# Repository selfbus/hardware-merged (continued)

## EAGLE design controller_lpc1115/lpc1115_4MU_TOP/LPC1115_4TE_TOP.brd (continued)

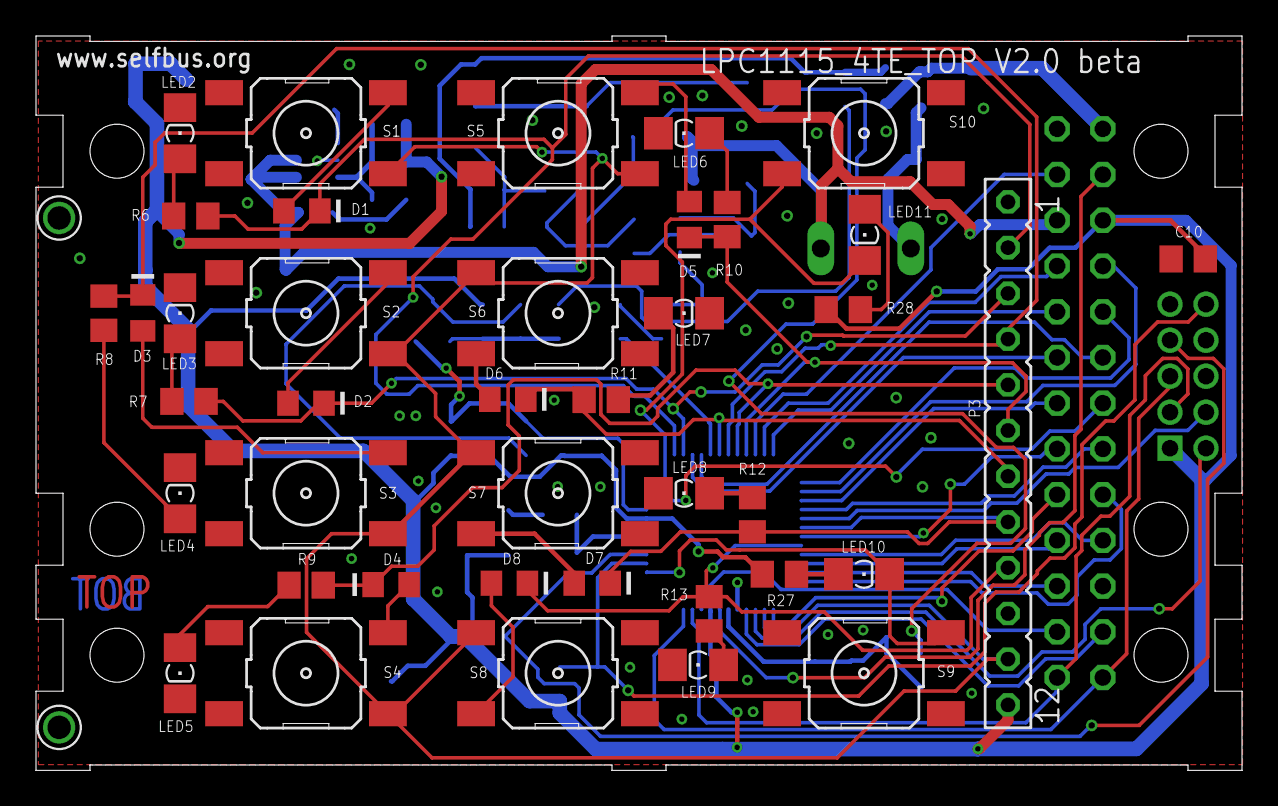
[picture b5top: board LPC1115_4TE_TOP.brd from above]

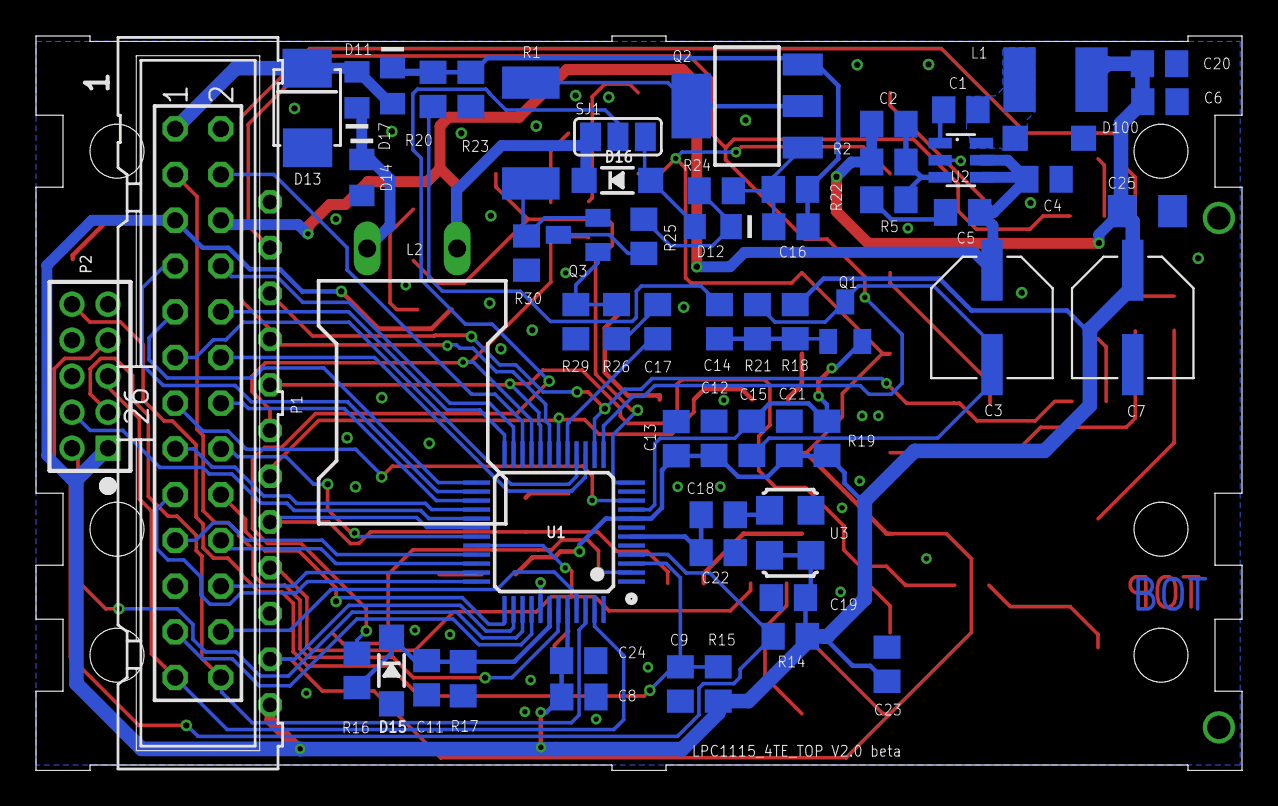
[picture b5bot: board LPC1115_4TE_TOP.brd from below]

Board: 2 copper layers, 67.0 x 40.8 mm, 103 parts (61 on the bottom side), 79 nets.

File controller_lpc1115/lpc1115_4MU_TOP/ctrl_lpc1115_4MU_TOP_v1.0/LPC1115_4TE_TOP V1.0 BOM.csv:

"Qty","Value","Package","Parts","Anmerkung","Lieferant","Bestellartikel","Artikelpreis","VPE","Postenpreis"
1,,"Platine LPC115_4TE_TOP",,,,,,,
1,,"ML26","P1",,"Reichelt","SL 2X13G 2,54","0,12",1,"0,12"
1,,"Pfostenbuchse 2x13pol 2,54mm",,,"Reichelt","PFL 26","0,19",1,"0,19"
1,"ISP","PINHD-2X05_2.00mm","P2",,"Reichelt","MPE 150-3-010","0,2",1,"0,2"
0,,"FE-1X12_2.54mm","P3","nur benötigt, wenn Bedienplatine aufgesteckt werden soll!","Reichelt","MPE 094-1-016","0,31",1,0
2,"18p","C-EUC0805M","C20, C21","wenn Quarz verwendet wird, vermutlich passen auch 15pF","TME","CC0805JRNPO9BN180","0,00973",1,"0,01946"
2,"100p","C-EUC0805M","C15, C18","C18: wenn Oszillator verwendet wird","Reichelt","NPO-G0805 100P","0,04",1,"0,08"
1,"220p","C-EUC0805M","C22","wenn Oszillator verwendet wird","Reichelt","NPO-G0805 220P","0,04",1,"0,04"
3,"10n","C-EUC0805M","C9, C16, C17"," ","Reichelt","X7R-G0805 10N","0,04",1,"0,12"
1,"10n(*)","C-EUC0805M","C11","Applikationsabhängig","Reichelt","X7R-G0805 10N","0,04",1,"0,04"
1,"15nF","C-EUC0805M","C1",,"Reichelt","X7R-G0805 15N","0,04",1,"0,04"
7,"100n","C-EUC0805M","C5, C8, C10, C12, C14, C19, C23",,"Reichelt","X7R-G0805 100N","0,04",1,"0,28"
1,"220n","C-EUC0805M","C2",,"Reichelt","X7R-G0805 0,22µ","0,04",1,"0,04"
1,"1µ/16V","C-EUC0805M","C13",,"Reichelt","X7R-G0805 1,0/16","0,04",1,"0,04"
1,"4.7µF/50V","C-EUC1206M","C4",,"Reichelt","X7R-G1206 4,7/50","0,23",1,"0,23"
1,"22µ/10V","C-EUC1210K","C6"," ","Reichelt","X7R-G1206 22/10","0,19",1,"0,19"
1,"FV 100/35 K-D8","CPOL-EUUD-6,3X7,7","C3",,"Reichelt","VF 100/35 K-D8","0,18",1,"0,18"
0,"100µ(*)","CPOL-EUUD-6,3X7,7","C7","abhängig vom Strombedarf der Applikation","Reichelt","VF 100/35 K-D8","0,18",1,0
1,"6.8µH","IND_FASTRON_1616FPSB","L1",,"Reichelt","L-1616FPS 6,8µ","0,3",1,"0,3"
1,"150mH","SD12BS11_LIEGEND","L2",,"Reichelt","L-11P 150M","0,55",1,"0,55"
1,"5R6","R-EU_R1206M","R30","RESISTOR, European symbol","Reichelt","SMD 1/4W 5,6","0,05",1,"0,05"
1,"680R","R-EU_R0805M","R5","RESISTOR, European symbol","Reichelt","SMD-0805 680","0,03",1,"0,03"
2,"1k","R-EU_R0805M","R22, R24","RESISTOR, European symbol","Reichelt","SMD-0805 1,00K","0,03",1,"0,06"
11,"1k5","R-EU_R0805M","R3, R6, R7, R8, R9, R10, R11, R12, R13, R27, R28","RESISTOR, European symbol","Reichelt","SMD-0805 1,50K","0,03",1,"0,33"
1,"2k2","R-EU_R0805M","R25","RESISTOR, European symbol","Reichelt","SMD-0805 2,20K","0,03",1,"0,03"
1,"2k4","R-EU_R0805M","R2","RESISTOR, European symbol","Reichelt","RND 0805 1 2,4K","0,02",1,"0,02"
1,"5k6","R-EU_R0805M","R26","RESISTOR, European symbol","Reichelt","SMD-0805 5,60K","0,03",1,"0,03"
2,"10k","R-EU_R0805M","R19, R20","RESISTOR, European symbol","Reichelt","SMD-0805 10,0K","0,03",1,"0,06"
1,"3k(*)","R-EU_R0805M","R17","RESISTOR, European symbol","Reichelt","RND 0805 1 3k0","0,02",1,"0,02"
1,"15k","R-EU_R0805M","R4","RESISTOR, European symbol","Reichelt","SMD-0805 15,0K","0,03",1,"0,03"
1,"47k","R-EU_R0805M","R21","RESISTOR, European symbol","Reichelt","SMD-0805 47,0K","0,03",1,"0,03"
1,"82k","R-EU_R0805M","R18","RESISTOR, European symbol","Reichelt","SMD-0805 82,0K","0,03",1,"0,03"
1,"36k(*)","R-EU_R0805M","R16","RESISTOR, European symbol","Reichelt","RND 0805 1 36k","0,02",1,"0,02"
4,"100k","R-EU_R0805M","R14, R15, R23, R29","RESISTOR, European symbol","Reichelt","SMD-0805 100K","0,03",1,"0,12"
1,"390k","R-EU_R0805M","R1","RESISTOR, European symbol","Reichelt","SMD-0805 390K","0,03",1,"0,03"
0,"SMAJ40CA","D-SMB","D13","nur wenn auf der Applikationsplatine keine vorhanden ist","Oldis Shop","SMAJ 40 AC Überspannungsdiode","0,2",1,0
12,"TS4148","DIODE-MINIMELF","D1, D2, D3, D4, D5, D6, D7, D8, D11, D12, D14, D17"," ","Reichelt","TS 4148-1206","0,04",1,"0,48"
0,"RB060M-60(*)","DIODE-SOD123","D9","nicht bestückt, es wird D10 verwendet",,,0,0,0
1,"STPS1L60A","DIODE-SMB","D10"," ","TME","STPS1L60A","0,089",1,"0,089"
0,"(*)","DIODE-MINIMELF","D15","Zenerdiode applikationsabhängig","Reichelt","SMD ZF 3,6","0,04",1,0
1,"7V5","ZENER-DIODESOT23","D16",,"Reichelt","SMD ZD 7,5","0,04",1,"0,04"
8,"grün","LEDSMT1206","LED2, LED3, LED4, LED5, LED6, LED7, LED8, LED9","extra helle LEDs, benötigen daher nur wenig Strom","Reichelt","LED EL 1206 GR2","0,12",1,"0,96"
2,"red","LEDSMT1206","LED1, LED10, LED11","üblicherweise wird nur eine der LEDs LED10, LED11 bestückt","Reichelt","LED EL 1206 RT","0,1",1,"0,2"
1,"BC856","BC856BSMD","Q1",,"Reichelt","BC 856B SMD","0,04",1,"0,04"
1,"BCP52","SOT223","Q2",,"Reichelt","BCP 52-16 SMD","0,14",1,"0,14"
1,"BC847C","BC847","Q3 (in V1.0 bedruckt mit T1)",,"Reichelt","BC 847C SMD","0,04",1,"0,04"
0,,"10-XXSMD","S1, S2, S3, S4, S5, S6, S7, S8","Benötigte Länge des Tasters abhängig von Applikation! (7mm ist Minimum, eher 8)","Reichelt","TASTER 9316","0,23",1,0
8,,"10-XXSMD","S1, S2, S3, S4, S5, S6, S7, S8","Taster 9318 8mm (Länge für out6-cs, jedoch nur 6 Stück notwendig)","Reichelt","TASTER 9318","0,21",1,"1,68"
1,"Prog","10-XXSMD","S9, S10","üblicherweise wird nur einer der beiden Taster bestückt","Reichelt","TASTER 9315","0,15",1,"0,15"
1,"LPC1115FBD48","LPC1113/4/5_QFP48_XLSERIES","U1","LPC1115FBD48 (auch bei TME zu bekommen)","Oldis Shop","NXP LPC1115","2,5",1,"2,5"
1,"BD9G101","BD9G101G-SOT23-6","U2","Schaltregler","Oldis Shop","Schaltregler BD9G101G-CT-ND","1,5",1,"1,5"
1,"XO32 12MHz","ASFL","U3","CRYSTAL CLOCK OSCILLATORS","Reichelt","XO32 12,00000","1,3",1,"1,3"
0,"12MHz","CRYSTALASF","X1","Quarz alternativ zum Oszillator! Der Reichelt-Typ hat 12pF statt 10pF Nenn","Reichelt","12,000000-MT","0,95",1,0
10,,,,"Lichtleiter 4,7mm (für out6-cs nur 8 Stück notwendig)","Conrad",183133,"0,65",1,"6,5"

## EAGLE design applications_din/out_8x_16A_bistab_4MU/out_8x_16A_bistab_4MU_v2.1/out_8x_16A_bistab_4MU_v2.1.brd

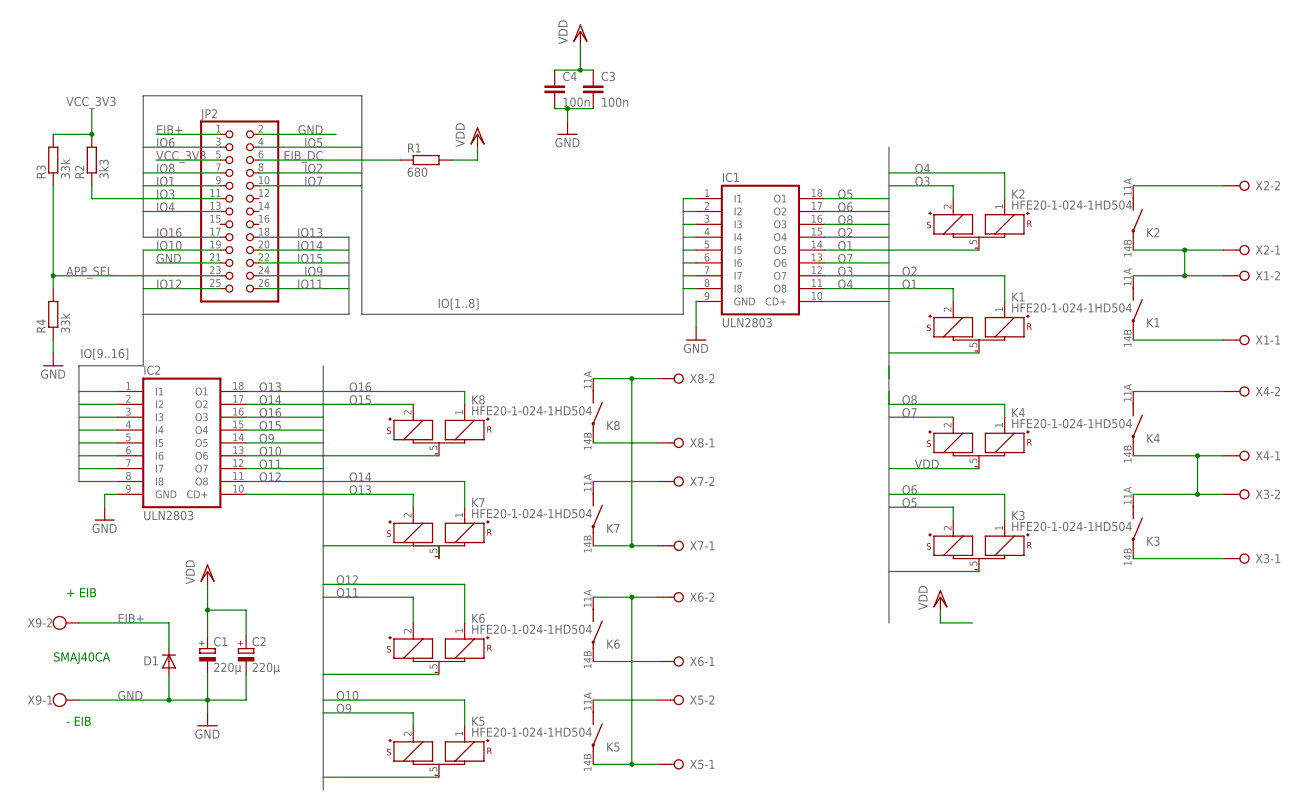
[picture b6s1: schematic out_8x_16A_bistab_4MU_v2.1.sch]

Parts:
C1, C2: 220µ; E3,5-8
C3, C4: 100n; C1206
D1: D-SMB; SMB
IC1, IC2: ULN2803; SO18W
JP2: PINHD-2X13_2.54-SMD; 2X13SMD
K1, K2, K3, K4, K5, K6, K7, K8: HFE20-1-024-1HD504; HFE20-3-504
R1: 680; M1206
R2: 3k3; M1206
R3, R4: 33k; M1206
X1, X2, X3, X4, X5, X6, X7, X8: W237-02P; W237-132
X9: W237-102

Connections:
APP_SEL: JP2.23, R3.1, R4.2
EIB+: D1.1 (C), JP2.1, X9.2
EIB_DC: JP2.6, R1.1
GND: C1.-, C2.-, C3.2, C4.2, D1.2 (A), IC1.9 (GND), IC2.9 (GND), JP2.2, JP2.21, R4.1, X9.1
IO1: IC1.5 (I5), JP2.9
IO2: IC1.4 (I4), JP2.8
IO3: IC1.7 (I7), JP2.11, R2.1
IO4: IC1.8 (I8), JP2.13
IO5: IC1.1 (I1), JP2.4
IO6: IC1.2 (I2), JP2.3
IO7: IC1.6 (I6), JP2.10
IO8: IC1.3 (I3), JP2.7
IO9: IC2.5 (I5), JP2.24
IO10: IC2.6 (I6), JP2.19
IO11: IC2.7 (I7), JP2.26
IO12: IC2.8 (I8), JP2.25
IO13: IC2.1 (I1), JP2.18
IO14: IC2.2 (I2), JP2.20
IO15: IC2.4 (I4), JP2.22
IO16: IC2.3 (I3), JP2.17
K12: K1.11A (PB), K2.14B (PA), X1.2, X2.1
K34: K3.11A (PB), K4.14B (PA), X3.2, X4.1
K56: K5.14B (PA), K6.11A (PB), X5.1, X6.2
K78: K7.14B (PA), K8.11A (PB), X7.1, X8.2
unnamed: K4.11A (PB), X4.2
unnamed: K8.14B (PA), X8.1
unnamed: K1.14B (PA), X1.1
unnamed: K3.14B (PA), X3.1
unnamed: K2.11A (PB), X2.2
unnamed: K7.11A (PB), X7.2
unnamed: K5.11A (PB), X5.2
unnamed: K6.14B (PA), X6.1
O1: IC1.14 (O5), K1.2 (S+)
O2: IC1.15 (O4), K1.1 (R+)
O3: IC1.12 (O7), K2.2 (S+)
O4: IC1.11 (O8), K2.1 (R+)
O5: IC1.18 (O1), K3.2 (S+)
O6: IC1.17 (O2), K3.1 (R+)
O7: IC1.13 (O6), K4.2 (S+)
O8: IC1.16 (O3), K4.1 (R+)
O9: IC2.14 (O5), K5.2 (S+)
O10: IC2.13 (O6), K5.1 (R+)
O11: IC2.12 (O7), K6.2 (S+)
O12: IC2.11 (O8), K6.1 (R+)
O13: IC2.18 (O1), K7.2 (S+)
O14: IC2.17 (O2), K7.1 (R+)
O15: IC2.15 (O4), K8.2 (S+)
O16: IC2.16 (O3), K8.1 (R+)
VCC_3V3: JP2.5, R2.2, R3.2
VDD: C1.+, C2.+, C3.1, C4.1, IC1.10 (CD+), IC2.10 (CD+), K1.5 (-), K2.5 (-), K3.5 (-), K4.5 (-), K5.5 (-), K6.5 (-), K7.5 (-), K8.5 (-), R1.2

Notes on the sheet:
+ EIB
- EIB
SMAJ40CA

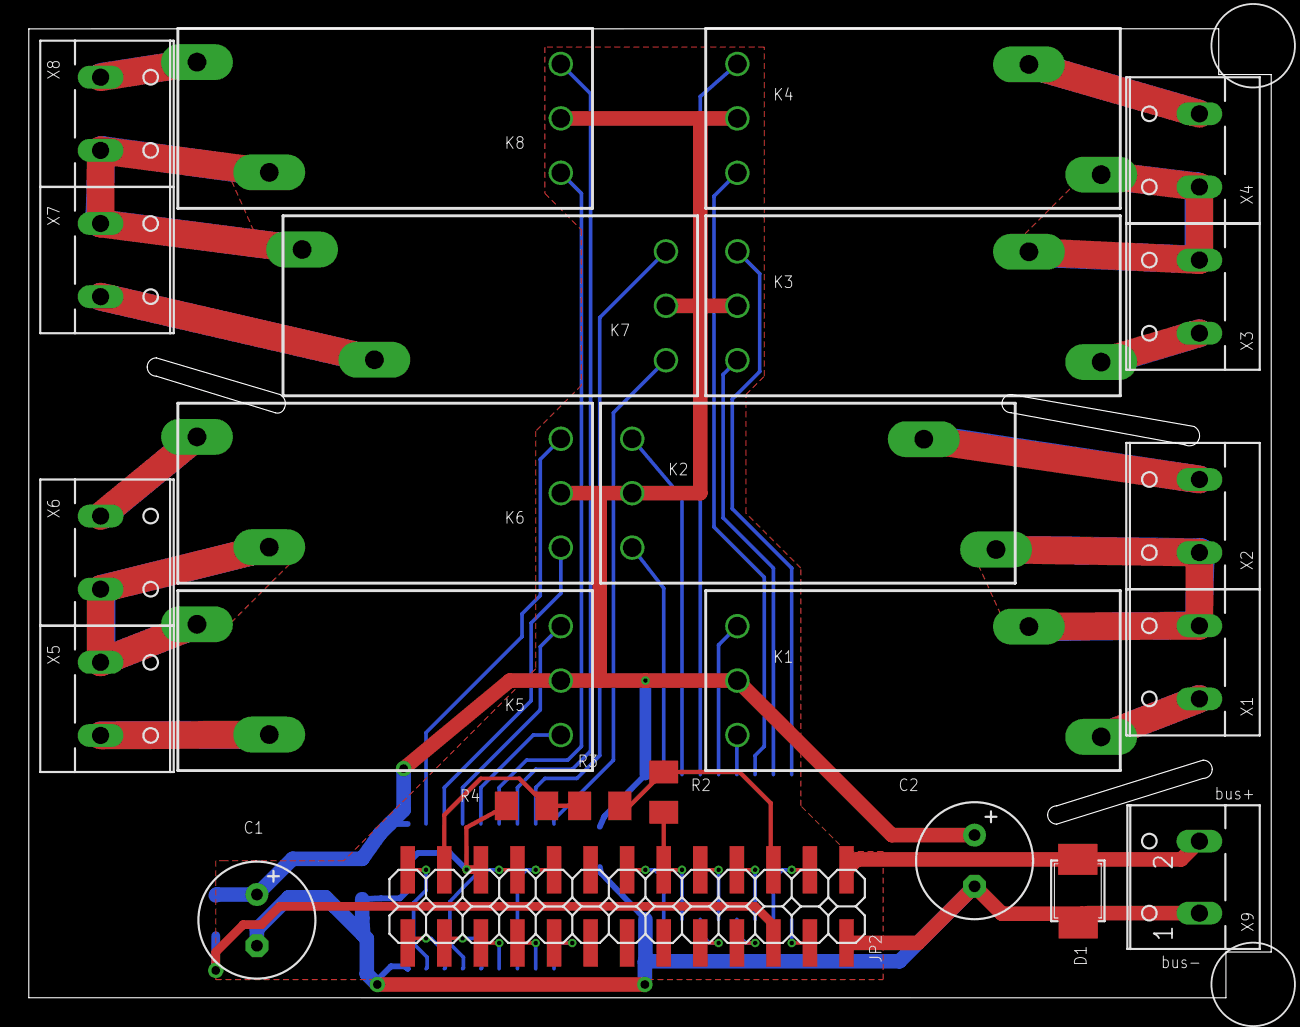
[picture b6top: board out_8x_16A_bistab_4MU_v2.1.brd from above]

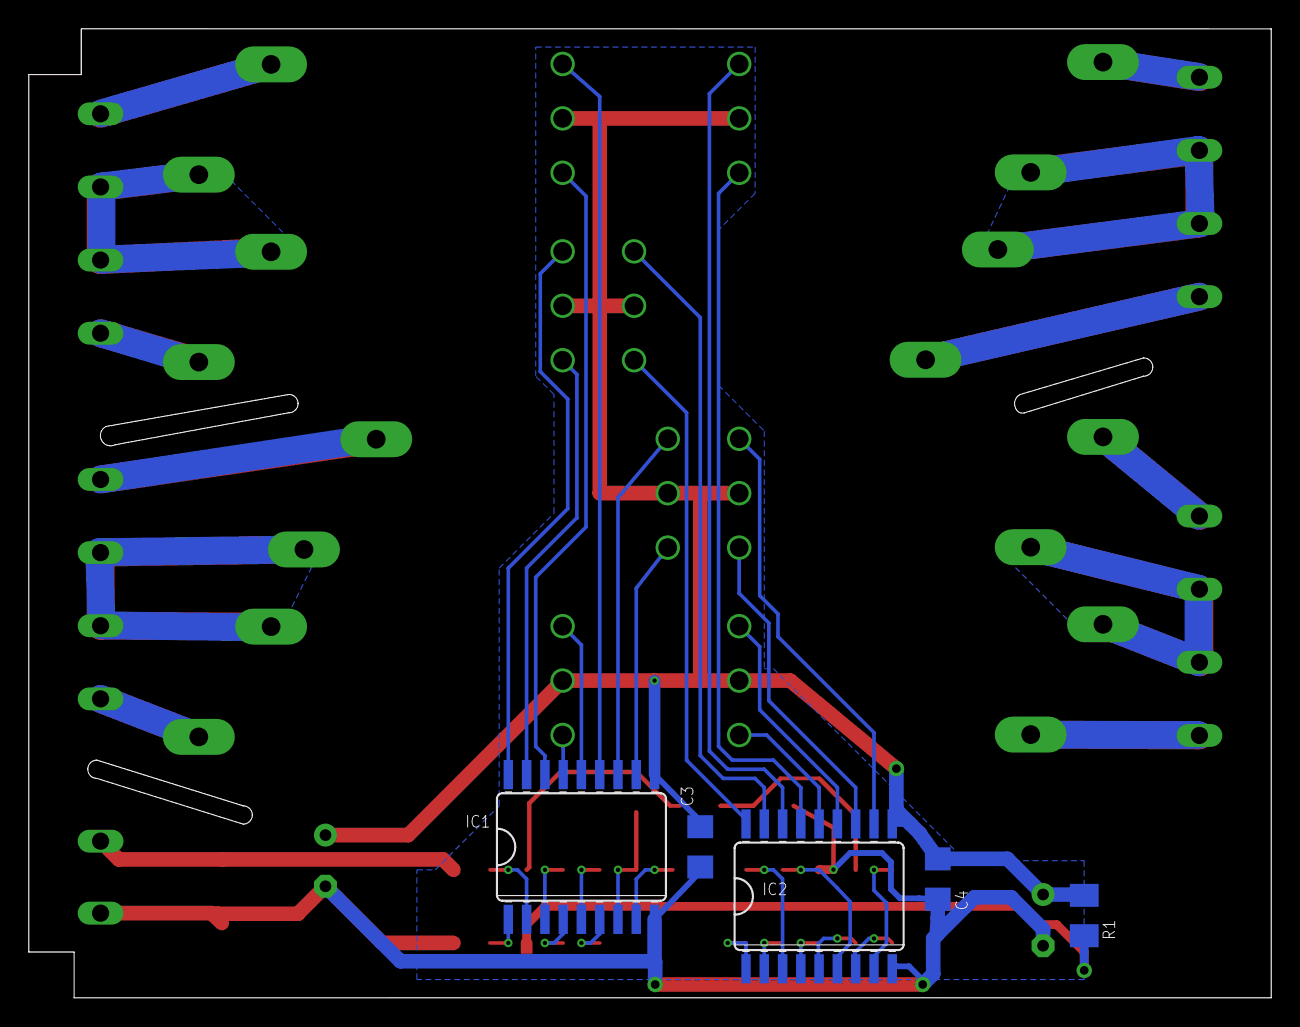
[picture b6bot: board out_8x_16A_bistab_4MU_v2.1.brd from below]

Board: 2 copper layers, 86.3 x 67.3 mm, 30 parts (5 on the bottom side), 50 nets.

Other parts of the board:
U$1: HUT4C-NO-DRILL

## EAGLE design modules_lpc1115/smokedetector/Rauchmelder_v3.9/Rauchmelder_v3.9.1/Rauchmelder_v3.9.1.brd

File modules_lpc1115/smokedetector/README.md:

<h1>KNX interface for Gira Dual Q smoke detectors</h1>

This module is a well tested interface to get your Dual Q smoke detectors connected to your KNX bus. 

The unversioned Rauchmelder.sch and Rauchmelder.brd files are the development files. 
Once a new version is released, a corresponding copy of the files with the release version appended to the file name are provided. 

Project documentation: https://selfbus.org/wiki/devices/sensors/6-smoke-detector-module </br>
Forum discussions: https://selfbus.org/forum/app.php/tag/Rauchmelder

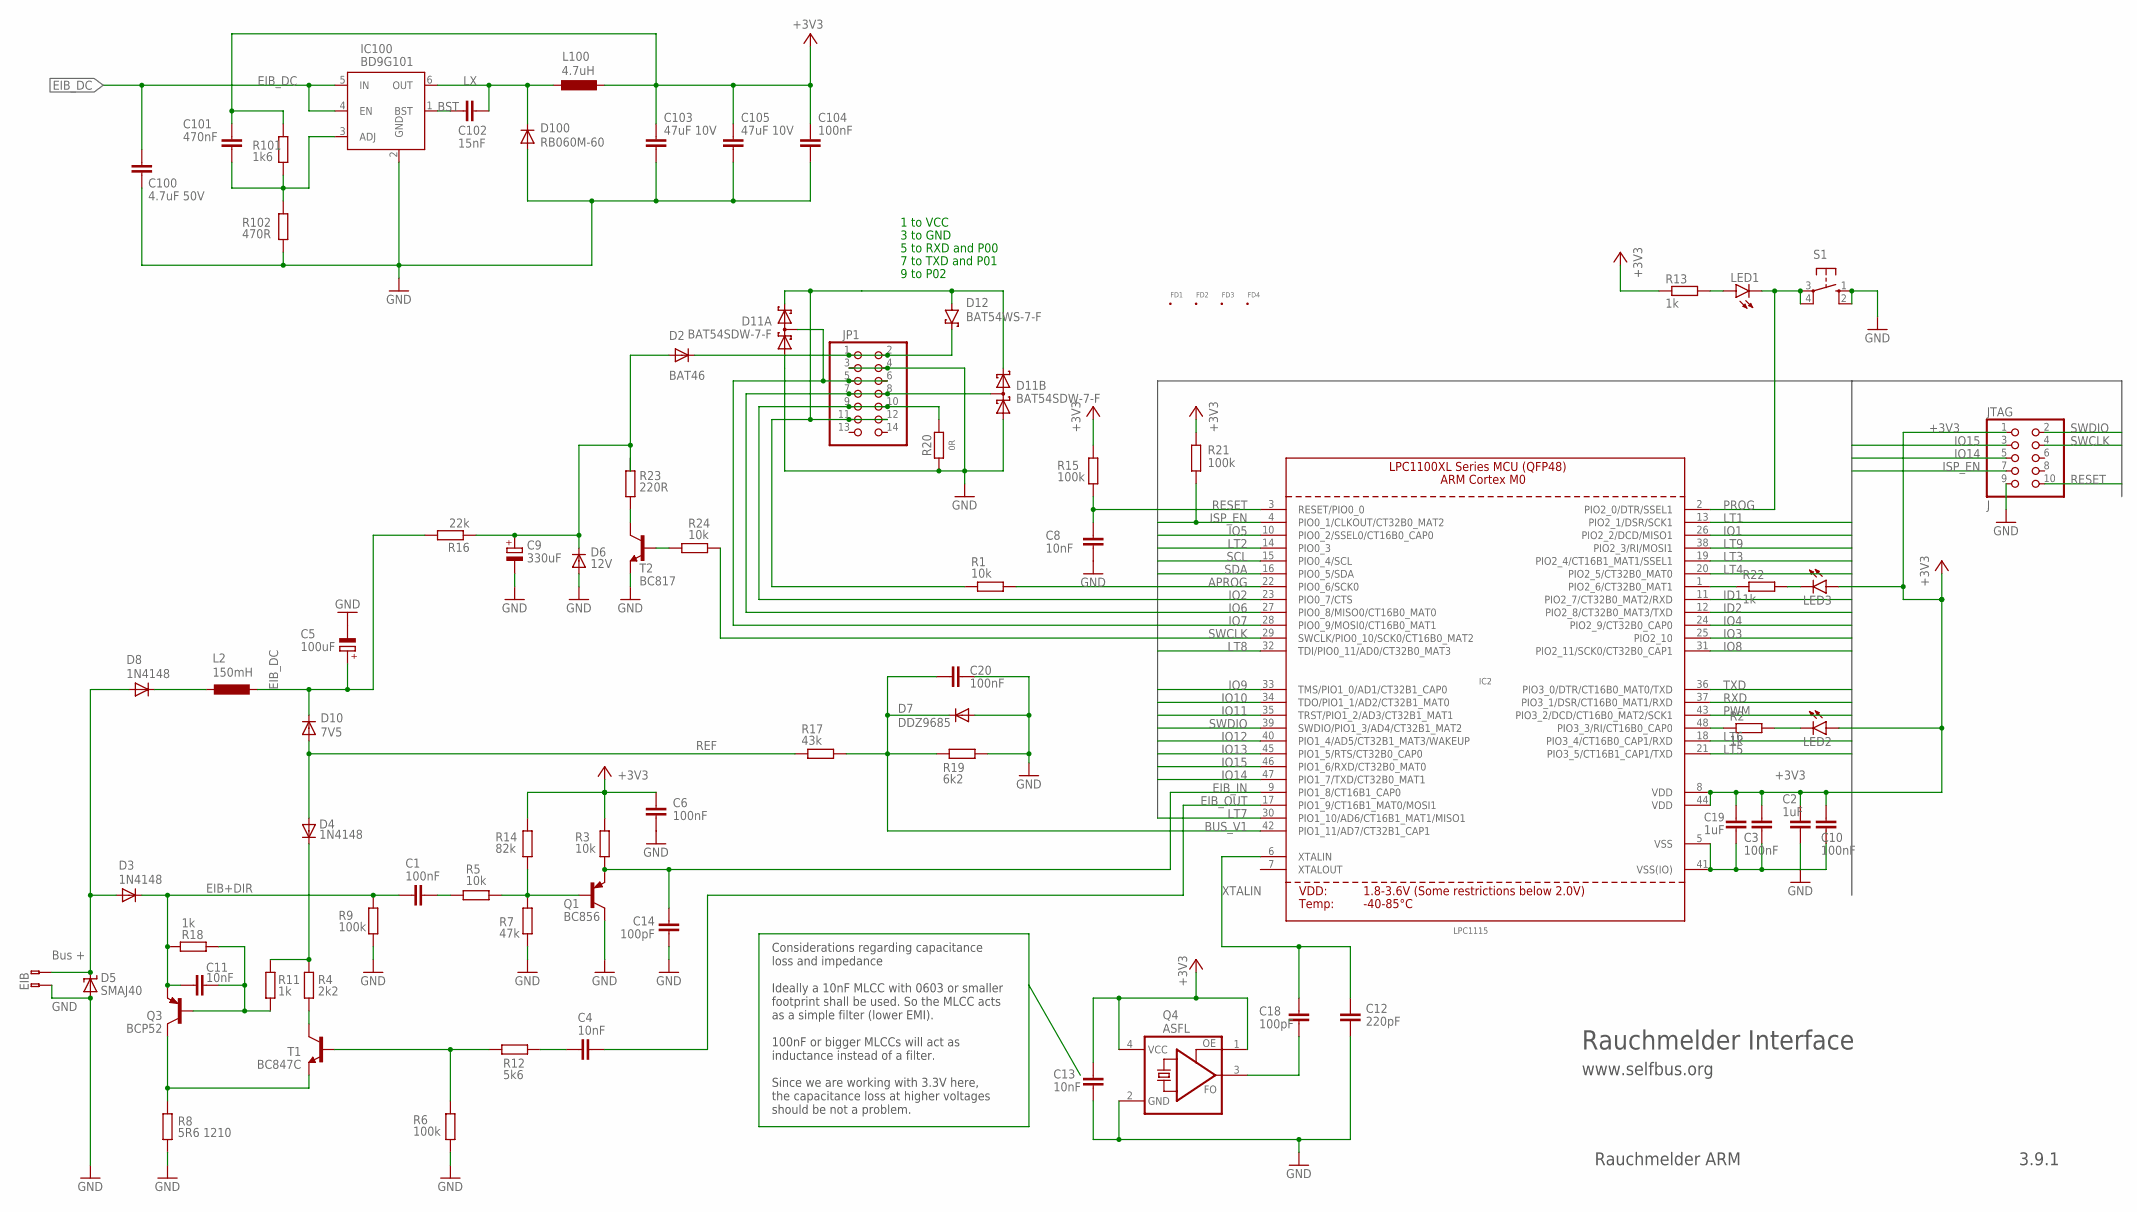
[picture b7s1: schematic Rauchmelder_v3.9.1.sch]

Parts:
C1, C3, C6, C10, C20, C104: 100nF; C0805
C2, C19: 1uF; C0805
C4, C8, C11, C13: 10nF; C0805
C5: 100uF; SANYO-OSCON_SMD_C6
C9: 330uF; E3,5-8
C12: 220pF; C0805
C14, C18: 100pF; C0805
C100: 4.7uF 50V; C1210
C101: 470nF; C0805
C102: 15nF; C0805
C103, C105: 47uF 10V; C0805
D2: BAT46; SOD-123
D3, D4, D8: 1N4148; SOD-123
D5: SMAJ40; SMBJ
D6: 12V; SOD-123
D7: DDZ9685; SOD-123
D10: 7V5; SOD-123
D11: BAT54SDW-7-F; SOT363
D12: BAT54WS-7-F; SOD323
D100: RB060M-60; SOD-123
FD1, FD2, FD3, FD4: FID_40MIL; FID_040
IC2: LPC1115; LQFP48
IC100: BD9G101; SOT23-6
JP1: PINHD-2X7; 2X07
JTAG: J; 2X05M
L2: 150mH; 11P-L1
L100: 4.7uH; L4532P
LED1, LED2, LED3: LEDCHIPLED_0805; CHIPLED_0805
Q1: BC856; SOT23-BEC
Q3: BCP52; SOT223
Q4: ASFL; ASF
R1, R3, R5, R24: 10k; R0805
R2, R11, R13, R18, R22: 1k; R0805
R4: 2k2; R0805
R6, R9, R15, R21: 100k; R0805
R7: 47k; R0805
R8: 5R6 1210; R1210
R12: 5k6; R0805
R14: 82k; R0805
R16: 22k; R0805
R17: 43k; R0805
R19: 6k2; R0805
R20: 0R; R0805
R23: 220R; R2512
R101: 1k6; R0805
R102: 470R; R0805
S1: 10-XX; B3F-10XX
T1: BC847C; SOT23
T2: BC817; SOT23-WIDE
U$1: EIB; BUSKLEMME243-724

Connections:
+3V3: C2.2, C3.2, C6.2, C10.2, C13.2, C19.2, C101.2, C103.1, C104.1, C105.1, IC2.8 (VDD), IC2.44 (VDD), JTAG.1, L100.2, LED2.A, LED3.A, Q4.1 (OE), Q4.4 (VCC), R3.2, R13.1, R14.2, R15.1, R21.2, R101.2
APROG: IC2.22 (PIO0_6/SCK0)
ARMINFO1: IC2.48 (PIO3_3/RI/CT16B0_CAP0), R2.1
ARMINFO2: IC2.1 (PIO2_6/CT32B0_MAT1), R22.1
BST: C102.2, IC100.1 (BST)
BUS_V1: C20.2, D7.C, IC2.42 (PIO1_11/AD7/CT32B1_CAP1), R17.2, R19.1
EIB+: D3.A, D5.C, D8.A, U$1.2 (B-2)
EIB+DIR: C1.1, C11.1, D3.C, Q3.3 (E), R9.2, R18.2
EIB_DC: C5.+, C100.2, D10.C, IC100.4 (EN), IC100.5 (IN), L2.2, R16.2
EIB_IN: C14.2, IC2.9 (PIO1_8/CT16B1_CAP0), Q1.E, R3.1
EIB_OUT: C4.2, IC2.17 (PIO1_9/CT16B1_MAT0/MOSI1)
FB1: C101.1, IC100.3 (ADJ), R101.1, R102.2
GND: C2.1, C3.1, C5.-, C6.1, C8.1, C9.-, C10.1, C12.1, C13.1, C14.1, C19.1, C20.1, C100.1, C103.2, C104.2, C105.2, D5.A, D6.A, D7.A, D11.1 (A), D11.4 (A), D100.A, IC2.5 (VSS), IC2.41 (VSS(IO)), IC100.2 (GND), JP1.3, JP1.4, JTAG.9, Q1.C, Q4.2 (GND), R6.1, R7.1, R8.1, R9.1, R19.2, R20.1, R102.1, S1.1 (S), S1.2 (S1), T2.2 (E), U$1.1 (B-1)
ID1: IC2.11 (PIO2_7/CT32B0_MAT2/RXD)
ID2: IC2.12 (PIO2_8/CT32B0_MAT3/TXD)
IO1: IC2.26 (PIO2_2/DCD/MISO1)
IO2: IC2.23 (PIO0_7/CTS)
IO3: IC2.25 (PIO2_10)
IO4: IC2.24 (PIO2_9/CT32B0_CAP0)
IO5: IC2.10 (PIO0_2/SSEL0/CT16B0_CAP0)
IO6: IC2.27 (PIO0_8/MISO0/CT16B0_MAT0)
IO7: IC2.28 (PIO0_9/MOSI0/CT16B0_MAT1)
IO8: IC2.31 (PIO2_11/SCK0/CT32B0_CAP1)
IO9: IC2.33 (TMS/PIO1_0/AD1/CT32B1_CAP0)
IO10: IC2.34 (TDO/PIO1_1/AD2/CT32B1_MAT0)
IO11: IC2.35 (TRST/PIO1_2/AD3/CT32B1_MAT1)
IO12: IC2.40 (PIO1_4/AD5/CT32B1_MAT3/WAKEUP)
IO13: IC2.45 (PIO1_5/RTS/CT32B0_CAP0)
IO14: IC2.47 (PIO1_7/TXD/CT32B0_MAT1), JTAG.5
IO15: IC2.46 (PIO1_6/RXD/CT32B0_MAT0), JTAG.3
ISP_EN: IC2.4 (PIO0_1/CLKOUT/CT32B0_MAT2), JTAG.7, R21.1
LT1: IC2.13 (PIO2_1/DSR/SCK1), R24.2
LT2: IC2.14 (PIO0_3)
LT3: IC2.19 (PIO2_4/CT16B1_MAT1/SSEL1)
LT4: IC2.20 (PIO2_5/CT32B0_MAT0)
LT5: IC2.21 (PIO3_5/CT16B1_CAP1/TXD), JP1.9, JP1.10, R20.2
LT6: IC2.18 (PIO3_4/CT16B0_CAP1/RXD)
LT7: IC2.30 (PIO1_10/AD6/CT16B1_MAT1/MISO1)
LT8: IC2.32 (TDI/PIO0_11/AD0/CT32B0_MAT3), R1.2
LT9: IC2.38 (PIO2_3/RI/MOSI1)
LX: C102.1, D100.C, IC100.6 (OUT), L100.1
unnamed: D11.2 (C), D11.5 (C), D12.A, JP1.11, JP1.12, R1.1
unnamed: Q1.B, R5.2, R7.2, R14.1
unnamed: LED3.C, R22.2
unnamed: C11.2, Q3.1 (B), R11.1, R18.1
unnamed: LED2.C, R2.2
unnamed: R23.2, T2.3 (C)
unnamed: R24.1, T2.1 (B)
unnamed: LED1.A, R13.2
unnamed: C9.+, D2.A, D6.C, R16.1, R23.1
unnamed: D8.C, L2.1
unnamed: C1.2, R5.1
unnamed: D2.C, D12.C, JP1.1, JP1.2
unnamed: C4.1, R12.1
unnamed: R4.1, T1.3 (C)
unnamed: D4.C, R4.2, R11.2
unnamed: Q3.2 (C), Q3.4 (C), R8.2, T1.2 (E)
unnamed: R6.2, R12.2, T1.1 (B)
unnamed: C18.1, Q4.3 (FO)
PROG: IC2.2 (PIO2_0/DTR/SSEL1), LED1.C, S1.3, S1.4 (P1)
PWM: IC2.43 (PIO3_2/DCD/CT16B0_MAT2/SCK1)
REF: D4.A, D10.A, R17.1
RESET: C8.2, IC2.3 (RESET/PIO0_0), JTAG.10, R15.2
RXD: D11.6 (AC), IC2.37 (PIO3_1/DSR/CT16B0_MAT1/RXD), JP1.5, JP1.6
SCL: IC2.15 (PIO0_4/SCL)
SDA: IC2.16 (PIO0_5/SDA)
SWCLK: IC2.29 (SWCLK/PIO0_10/SCK0/CT16B0_MAT2), JTAG.4
SWDIO: IC2.39 (SWDIO/PIO1_3/AD4/CT32B1_MAT2), JTAG.2
TXD: D11.3 (AC), IC2.36 (PIO3_0/DTR/CT16B0_MAT0/TXD), JP1.7, JP1.8
XTALIN: C12.2, C18.2, IC2.6 (XTALIN)

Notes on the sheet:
Bus +
GND
Rauchmelder Interface
www.selfbus.org
Rauchmelder ARM
3.9.1
5 to RXD and P00
7 to TXD and P01
9 to P02
1 to VCC
3 to GND
Considerations regarding capacitance loss and impedance Ideally a 10nF MLCC with 0603 or smaller footprint shall be used. So the MLCC acts as a simple filter (lower EMI). 100nF or bigger MLCCs will act as inductance instead of a filter. Since we are working with 3.3V here, the capacitance loss at h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

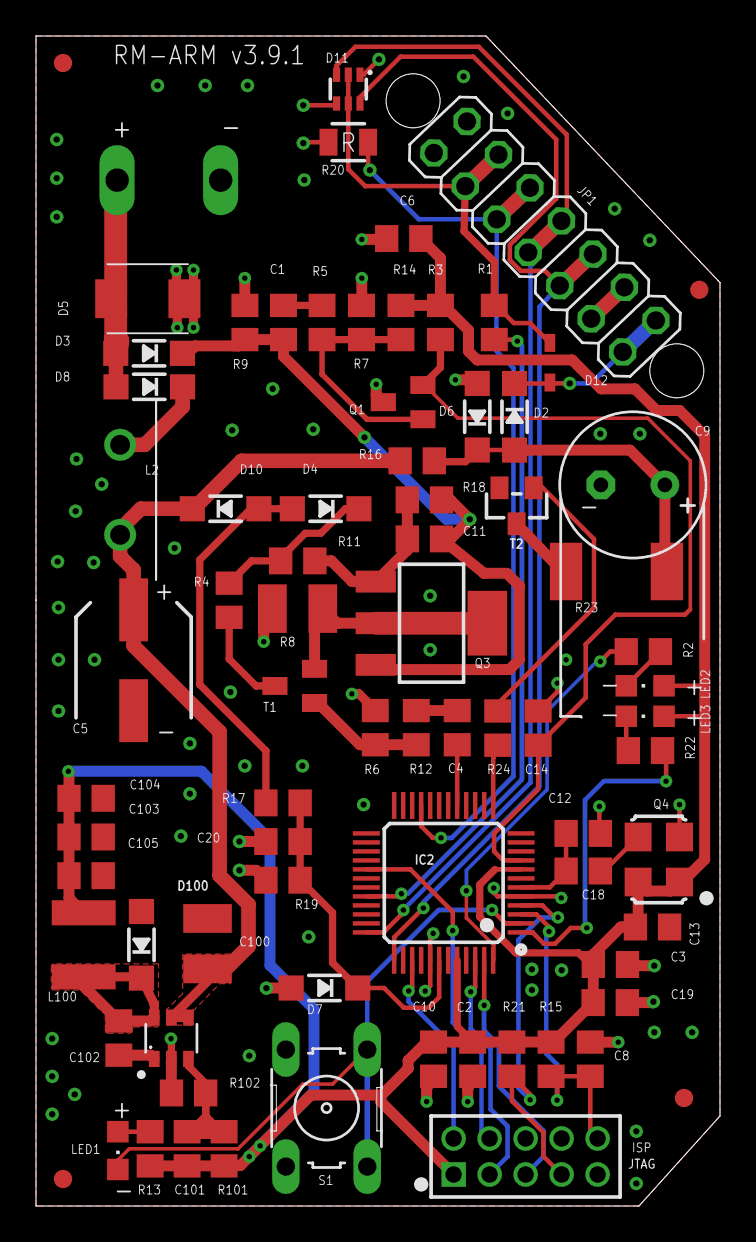
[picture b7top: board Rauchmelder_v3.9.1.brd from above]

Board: 2 copper layers, 38.0 x 65.0 mm, 78 parts (0 on the bottom side), 45 nets.

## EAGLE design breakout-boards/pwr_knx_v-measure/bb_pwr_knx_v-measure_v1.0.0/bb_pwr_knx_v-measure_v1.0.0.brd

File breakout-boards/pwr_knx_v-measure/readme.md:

<h1>Breakoutboard providing power, KNX bus reading and sending circuits, KNX bus voltage measure components</h1>

The unversioned *.sch and *.brd files are the development files. 
Once a new version is released, a corresponding copy of the files with the release version appended to the file name are provided. 

Project documentation: https://selfbus.org/wiki/hardware/33-break-out-boards/85-breakout-board-zur-stromversorgung-buskommunikation-und-busspannungsmessung</br>
Forum discussions: https://selfbus.org/forum/app.php/tag/breakoutboard

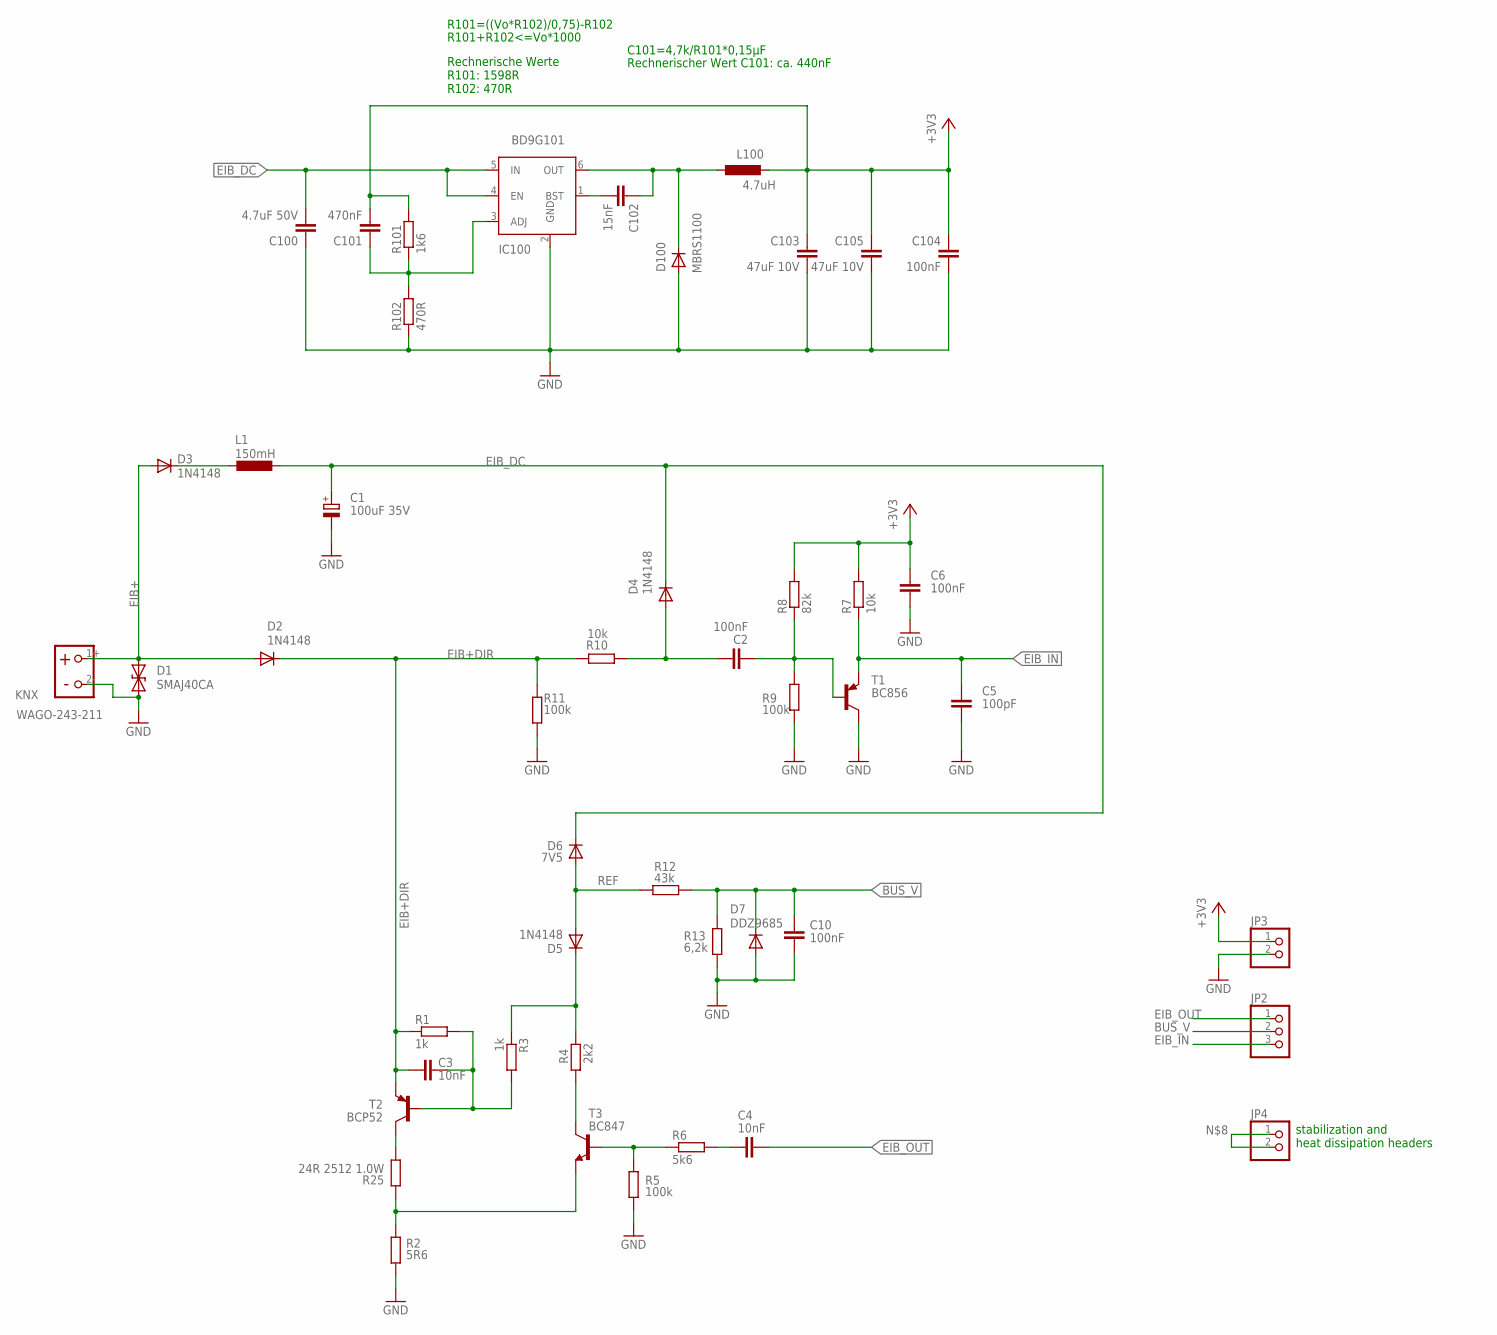
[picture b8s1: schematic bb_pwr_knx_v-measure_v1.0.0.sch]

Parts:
C1: 100uF 35V; SANYO-OSCON_SMD_C6
C2, C6, C10, C104: 100nF; C0805
C3, C4: 10nF; C0805
C5: 100pF; C0805
C100: 4.7uF 50V; C0805
C101: 470nF; C0805
C102: 15nF; C0805
C103, C105: 47uF 10V; C0805
D1: SMAJ40CA; DO214AC
D2, D3, D4, D5: 1N4148; SOD-123
D6: 7V5; SOD-123
D7: DDZ9685; SOD-123
D100: MBRS1100; SOD-123
IC100: BD9G101; SOT23-6
JP2: PINHD-1X3; 1X03
JP3, JP4: PINHD-1X2; 1X02
KNX: WAGO-243-211
L1: 150mH; 11P-L1
L100: 4.7uH; L4532P
R1, R3: 1k; R0805
R2: 5R6; R0805
R4: 2k2; R0805
R5, R9, R11: 100k; R0805
R6: 5k6; R0805
R7, R10: 10k; R0805
R8: 82k; R0805
R12: 43k; R0805
R13: 6,2k; R0805
R25: 24R 2512 1.0W; R2512
R101: 1k6; R0805
R102: 470R; R0805
T1: BC856; SOT23-BEC
T2: BCP52; SOT223
T3: BC847; SOT23

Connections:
+3V3: C6.2, C101.2, C103.1, C104.1, C105.1, JP3.1, L100.2, R7.2, R8.2, R101.2
BST: C102.2, IC100.1 (BST)
BUS_V: C10.2, D7.C, JP2.2, R12.2, R13.1
EIB+: D1.C (2), D2.A, D3.A, KNX.1+
EIB+DIR: C3.1, D2.C, R1.1, R10.2, R11.2, T2.3 (E)
EIB_DC: C1.+, C100.2, D4.C, D6.C, IC100.4 (EN), IC100.5 (IN), L1.2
EIB_IN: C5.2, JP2.3, R7.1, T1.E
EIB_OUT: C4.2, JP2.1
FB: C101.1, IC100.3 (ADJ), R101.1, R102.2
GND: C1.-, C5.1, C6.1, C10.1, C100.1, C103.2, C104.2, C105.2, D1.A (1), D7.A, D100.A, IC100.2 (GND), JP3.2, KNX.2-, R2.1, R5.2, R9.1, R11.1, R13.2, R102.1, T1.C
LX: C102.1, D100.C, IC100.6 (OUT), L100.1
unnamed: C2.2, D4.A, R10.1
unnamed: D3.C, L1.1
unnamed: C4.1, R6.2
unnamed: R4.1, T3.3 (C)
unnamed: R2.2, R25.1, T3.2 (E)
unnamed: JP4.1, JP4.2, R25.2, T2.2 (C), T2.4 (C)
unnamed: R5.1, R6.1, T3.1 (B)
unnamed: C2.1, R8.1, R9.2, T1.B
unnamed: C3.2, R1.2, R3.2, T2.1 (B)
unnamed: D5.C, R3.1, R4.2
REF: D5.A, D6.A, R12.1

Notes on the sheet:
R101=((Vo*R102)/0,75)-R102
R101+R102<=Vo*1000
Rechnerische Werte R101: 1598R R102: 470R
C101=4,7k/R101*0,15µF
Rechnerischer Wert C101: ca. 440nF
stabilization and heat dissipation headers

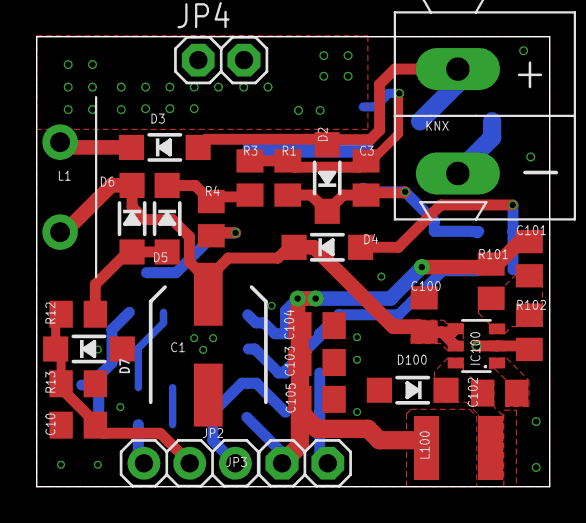
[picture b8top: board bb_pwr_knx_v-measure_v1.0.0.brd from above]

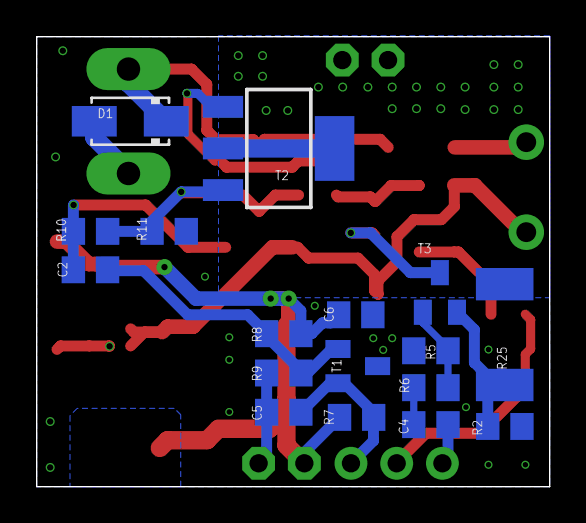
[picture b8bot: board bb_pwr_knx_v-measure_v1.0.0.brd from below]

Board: 2 copper layers, 28.5 x 25.0 mm, 47 parts (17 on the bottom side), 22 nets.
